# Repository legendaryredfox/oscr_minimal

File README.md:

# oscr_minimal — dumper de cartuchos SNES / NES / Famicom / Mega Drive / GBA

*English summary: [`README.en.md`](README.en.md).*

Shield para **Arduino Mega 2560 (R3)** que lê ROMs e saves de cartuchos pela USB, direto para o PC.
Sem LCD, sem cartão SD. Somente um cartucho por vez.

> **Estado:** 8 placas com projeto KiCad e gerbers, firmware (fork do OSCR com protocolo serial), CLI Python, CLI e GUI em Kotlin (pt-BR, en, ru, zh). **Nenhuma placa foi montada e nada foi testado com cartucho real**: só os testes automáticos no PC e as verificações de hardware abaixo rodaram. Ver "O que foi testado e o que falta".

## Atribuição

Baseado no **Open Source Cartridge Reader (OSCR)** de sanni e comunidade.

- Hardware original: <https://github.com/sanni/cartreader> (licença **CC BY 4.0**).
  Upstream atual: <https://github.com/oscartreader>.
- Firmware original: GPL v3. O firmware deste projeto continuará GPL v3.
- Slots (símbolos e footprints) copiados do OSCR, com alterações descritas em `boards/_lib/README.md`.

Adaptado por: <https://github.com/legendaryredfox/oscr_minimal>

## Conteúdo

| Pasta | O que tem |
|---|---|
| `CLAUDE.md` | Decisões de projeto e fases (também serve de instrução para assistentes de código) |
| `boards/` | **Variantes de hardware**, uma pasta cada (índice e estado em `boards/README.md`). Com projeto KiCad e gerbers: `16_and_8_bits/` (5 slots), `16_bits/` (SNES e Mega Drive) e as de um sistema só ou de dois: `megadrive/`, `snes/`, `nes/`, `famicom/`, `famicom_nes/`, `8_bits/` (NES, Famicom e Master System), `gb_gba/`, `completa/` (sete slots) |
| `boards/<placa>/docs/pinmap.md` | **Fonte da verdade** de cada placa: pino do slot → pino do Mega (o da `16_and_8_bits` é gerado por `tools/gen_pinmap.py`; os das outras são recortes dele) |
| `docs/decisoes.md` | Log de decisões, desvios e pendências |
| `boards/<placa>/hardware-<versão>/` (uma pasta por versão), `fab/`, `docs/` | Projeto KiCad 10 (`dumper.kicad_pro/_sch/_pcb`), gerbers e zip da JLCPCB (`fab/PEDIDO.md` diz como pedir) e `bom.md`/`montagem.md` de cada placa |
| `boards/_lib/` | Símbolos e footprints KiCad compartilhados entre as variantes |
| `docs/referencia/uso.md` | **Guia de uso**: casos de uso, cenários por sistema e solução de problemas |
| `docs/historico/revisao-codigo.md` | Revisão de código da base toda (achados, gravidade, o que foi corrigido) |
| `docs/historico/revisao-ux.md` | Revisão de UX/UI da GUI, da CLI e do hardware, com capturas de tela |
| `docs/referencia/protocolo.md`, `docs/referencia/cli.md`, `docs/referencia/fork-oscr.md`, `docs/referencia/funcoes-oscr.md` | Protocolo serial, guia da CLI, plano do fork do firmware e inventário das funções do OSCR |
| `docs/planos/placa-v1.3-rp2040.md`, `firmware/cic_rp2040/` | CIC do SNES com RP2040-Zero no lugar do PIC (ainda não validado; as placas atuais usam o PIC12F629) |
| `firmware/`, `host/`, `gui/` | Comuns a todas as variantes |
| `database/oscr/` | Base de jogos (24 007, CRC32) do OSCR legado, GPL v3, mais `json/` (bases do `oscr-databases`, 4,9 mil CRC32 novos; o repositório de origem não declara licença, D127); carregada sozinha pelo host e pela GUI (D88, D127) |
| `tools/` | Scripts de hardware: `check_netlist.py` (`--board <placa>`), `export_fab.sh`, `gen_pinmap.py`, `build_lib.py`, `fill_zones.py` e os de cada placa (`megadrive/`, `snes/`, `nes/`, `famicom/`, `famicom_nes/`, `gb_gba/`, `revisao/`); ver `tools/README.md` |

## Adaptadores e repositórios de referência

O código de leitura dos cartuchos vem do OSCR; o que muda por sistema é o adaptador. Fontes consultadas e adaptadores que o firmware reconhece (D136, D137):

| Referência | Para quê |
|---|---|
| <https://github.com/sanni/cartreader> (pasta `hardware/`: `mastersystem_adapter`, `six_slot_adapter`, `*_adapter`) | KiCad dos adaptadores do OSCR; o slot Master System da `megadrive_sms` e os footprints dos slots vêm daí (CC BY 4.0). Arquivado desde 2026-06 |
| <https://github.com/oscartreader/oscr-firmware> | firmware atual do OSCR (GPL v3), base do fork em `firmware/oscr/` |
| <https://github.com/oscartreader/oscr-databases> | bases de jogos e a tabela de chips de flash (`database/oscr/`, D127 e D135; sem licença declarada) |
| <https://github.com/oscartreader/oscr-hardware> | repositório de hardware do novo upstream (vazio em 2026-11-08) |
| <https://github.com/sanni/cartreader/discussions/874> | discussão do adaptador de Game Gear (slot com o conector do RetroSix) |
| <https://www.raphnet.net/electronique/sms_cartridge_programmer/index_en.php> | adaptador **Raphnet** de Master System / SG-1000 (modo `SMSRaphnet` e `SG1000Raphnet` do `SMS.cpp`) |
| <https://forum.retrode.com> | adaptadores **Retrode** (`SMSRetrode`, `GGRetrode` do `SMS.cpp`) |
| <https://www.retrosix.wiki> | pinagem do cartucho de Game Gear e de outros consoles Sega |
| <https://www.smspower.org/maxim/Documents/Pinouts> | pinagem do conector de cartucho do Master System, Mark III e SG-1000 |

**Game Gear e SG-1000** não têm slot próprio nas placas deste projeto: usam adaptador no slot Mega Drive (Retron 3in1, Retrode, Raphnet). Os adaptadores que achei são comerciais; **não encontrei arquivos abertos** (KiCad) deles. Se aparecer um adaptador de código aberto, acrescente o link aqui.

**Tensão dos adaptadores (D138).** Os slots são de 5 V; os flashcarts comuns de Mega Drive e Master System precisam disso (regulam 3,3 V por dentro). As placas v1.1 de Mega Drive, SMS, NES e Famicom têm o **seletor 3,3 V/5 V** (padrão 5 V, `--voltage 3v3` para 3,3 V, alerta ao passar de 3,3 V para 5 V) e o jumper J1 \"TRAVA 3,3 V\"; todas as placas têm o fusível F1 (5×20 mm, 500 mA, em suporte de clipes, troca sem solda) opcional. Adaptador de Game Gear ou cartucho de 3,3 V: confira a tensão do adaptador antes de ligar. Detalhes: `docs/decisoes.md` D138.

## Aviso

- **Use por sua conta e risco.** Hardware e software saem sem garantia (CC BY 4.0 e GPL v3). Placas e firmware são experimentais.
- **Um cartucho por vez.** As placas levam 5 V aos slots de SNES, NES, Famicom e Mega Drive; só o slot GBA é 3,3 V (regulador próprio). Desligue o USB antes de trocar de cartucho e **não use adaptador de GB/GBA** em placa sem o slot GBA.
- **Gravar ROM apaga o chip**, e abortar no meio deixa o chip pela metade. Faça backup do save antes de gravar e comece por cartuchos sem valor (`docs/referencia/uso.md`, seção 7).
- **Uso legal.** A ferramenta serve para fazer cópia de segurança dos cartuchos que você possui. Este repositório não distribui ROMs, BIOS nem chaves; `database/oscr/` só tem listas de nomes e CRC32 do OSCR.
- Nintendo, Super Nintendo, Famicom, Game Boy, Sega, Mega Drive e outros nomes são marcas dos seus donos, citadas só para dizer com o que o projeto é compatível. Sem vínculo com essas empresas nem com o projeto OSCR.

## O que foi testado e o que falta

Cobertura medida (Python 90 %, Kotlin 91,7 % das linhas, C++ puro no PC) e o que nenhum teste alcança: [`docs/referencia/cobertura-testes.md`](docs/referencia/cobertura-testes.md).

**Testado (2026-11-06; tudo no PC, nada em hardware):**

| Parte | O que rodou | Resultado |
|---|---|---|
| Host Python (`host/`) | `cd host && python3 -m pytest -q` | 142 testes passam |
| Firmware, núcleos testáveis no PC | `make -C firmware/oscr/pc-tests test` (protocolo, sessão, plano do SNES, núcleo de flash do Mega Drive etc.) | passam (inclui 21 verificações do plano do SNES e 734 do núcleo de flash do Mega Drive) |
| Firmware, compilação | `pio run -e SerialASCII` em `firmware/oscr` | compila para o Mega 2560 |
| GUI e CLI Kotlin | `cd gui && ./gradlew :shared:jvmTest :desktopApp:compileKotlin :cliApp:compileKotlin` | testes passam, os dois módulos compilam; a janela foi vista só em display virtual |
| Placas (as 8) | ERC, DRC (`--schematic-parity`) e `tools/check_netlist.py --board <placa>` | ERC sem violações; DRC sem erros nem ligações abertas (só avisos de biblioteca e de paridade); netlist confere com o `pinmap.md` de cada placa |
| Gerbers | `16_bits` v1.0 (a antiga `rev2`, D110): zip idêntico ao exportado de `hardware-v1.0`; prévias 3D das placas novas vistas | ok |
| CI (`.github/workflows/ci.yml`) | **nunca executou**; a primeira execução será ao publicar | pendente |

**Falta (nada disso foi feito):**

- **Hardware.**
  - Montar uma placa, medir continuidade e tensão e rodar o primeiro dump (SNES LoROM, NES mapper 0 ou um Mega Drive simples) comparando o CRC32 com o No-Intro.
  - Conferir com as peças reais as medidas dos slots e do módulo Si5351 (D17, D23), o lado da etiqueta (D27, D28) e a altura dos espaçadores (D25).
  - Revisar à mão, no KiCad, os layouts feitos por autoroteador (`megadrive`, `snes`, `nes`, `famicom`, `famicom_nes`, `gb_gba`).
  - A única placa encomendada até agora é a `16_bits` v1.0 original (trilhas de alimentação em 0,3 mm); o repositório guarda no lugar dela a v1.0 revisada, a antiga `rev2` (D110).
- **Firmware.** Os núcleos do OSCR só rodam no AVR, então nenhum teste os cobre. Pontos prováveis de ajuste: tempos de leitura do NES, 1.000.000 baud, `Power::setVoltage` sem VSELECT e o laço de gravação de flash. Roteiro e ordem de risco das gravações em `docs/referencia/uso.md`, seção 7.
- **GUI e CLI.** Serial a 1.000.000 baud em Linux, macOS e Windows, janela estreita, revisão das traduções ru e zh por falantes nativos, empacotamento (deb/AppImage, dmg, msi). `save-write` ainda não relê o save depois de gravar.
- **Funções do OSCR que faltam** (SF Memory, Satellaview, mais mappers do NES, outros sistemas etc.): `docs/referencia/funcoes-oscr.md`.
- **Próximas sessões:** revisão do código, gravar o firmware no Arduino pelo programa desktop e pela CLI (hoje é com o PlatformIO), e testes com as placas.

## CIC do SNES: alternativas ao chip de 8 pinos

As placas com SNES usam hoje o **PIC12F629** (DIP-8, em soquete, gravado com o `snescic-lock-resync.hex` do OSCR). Estamos **estudando alternativas ao CIC de 8 pinos**; a mais avançada é um RP2040-Zero que roda o mesmo programa num interpretador (`docs/planos/placa-v1.3-rp2040.md`, `firmware/cic_rp2040/`, D89). Nada disso foi validado em hardware, e o PIC continua sendo o caminho suportado.

## Verificação

```
python3 tools/check_netlist.py --board <placa>        # netlist do esquemático vs boards/<placa>/docs/pinmap.md
kicad-cli sch erc boards/<placa>/hardware/dumper.kicad_sch                # ERC
kicad-cli pcb drc --schematic-parity boards/<placa>/hardware/dumper.kicad_pcb   # DRC
tools/export_fab.sh <placa> v1.0                      # gerbers, furos, BOM e zip em boards/<placa>/fab/
```

## Recriar o `vendor/` (não versionado)

```
mkdir -p vendor/oscr && cd vendor/oscr
git clone --depth 1 https://github.com/sanni/cartreader legacy
git clone --depth 1 https://github.com/oscartreader/oscr-firmware firmware
```

`tools/gen_pinmap.py` lê `vendor/oscr/legacy/` (pinout.ods, esquemáticos KiCad, firmware).

## Contribuir

Veja `CONTRIBUTING.md`. Testes em hardware são o que mais ajuda: abra uma issue com o modelo "Teste em hardware" (placa, cartucho, versão, logs).

## Requisitos

KiCad 10.0.8 (`kicad-cli`), Python 3.11+. Para refazer layouts: o servidor MCP do KiCad (Python com `pcbnew`) e o Freerouting; ver `tools/README.md` e `docs/decisoes.md` (D92 a D101).

## Licença

Hardware: **CC BY 4.0**. Software: **GPL v3 ou posterior**. Mesmas licenças do OSCR; ver `LICENSE.md`.

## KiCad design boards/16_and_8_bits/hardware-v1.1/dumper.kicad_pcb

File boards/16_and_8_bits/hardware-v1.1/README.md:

# 16_and_8_bits v1.1

Versão **v1.1** da placa [`16_and_8_bits`](../README.md): shield 100% THT para Arduino Mega 2560 R3, só USB. Esta é a versão mais nova.

| | |
|---|---|
| Slots | SNES (62p), NES (72p), Famicom (60p), Mega Drive (64p), todos a 5 V, e GBA (32p, SMD, 1,5 mm) a 3,3 V (regulador U3) |
| Circuitos | Si5351 em header fêmea e PIC12F629 (CIC do SNES) em soquete. |
| Tamanho | 144,1 × 134,1 mm |
| Projeto KiCad | [`hardware-v1.1/`](.) (`dumper.kicad_pro`, `.kicad_sch`, `.kicad_pcb`) |
| Fábrica (JLCPCB) | `../fab/gerbers-v1.1/`, `../fab/dumper-v1.1-jlcpcb.zip` |
| Renders | `render-cima.png`, `render-baixo.png` |
| Estado | Nada montado nem testado com cartucho; revisar o layout no KiCad antes de encomendar |

## Troca de cartucho

O 5V dos slots vai direto do Mega e **não é cortado por software** (o desligamento por software foi retirado, D139). Para trocar o cartucho, **desligue a placa tirando o cabo USB** do Mega; nunca com a USB ligada.

## Proteção de corrente e tensão (D138)

**F1: fusível de vidro 5×20 mm de 500 mA (ação rápida) em suporte de clipes, opcional.** O suporte é de furo passante (Littelfuse série 100 ou equivalente) e o fusível queimado se troca **sem solda**; fica em série com o 5 V que a placa recebe do Mega Um curto no cartucho queima o fusível e protege a placa, o Mega e a porta USB. A queda é de 0,1 a 0,2 V a 200 mA (o SA-1 do SNES continua abaixo de ~5,2 V). **Sem o fusível no suporte a placa fica sem 5 V** (um fio no lugar dele também serve). Ele limita corrente e não protege contra tensão errada.

**Seletor de tensão 3,3 V/5 V dos slots NES, Famicom, Mega Drive** (LDO LD1117V33 em TO-220, Q4 de bypass, Q5 de carga, comando no D18; sem resistores em série entre o Mega e os slots, D140). **Padrão: 5 V**; 3,3 V só quando o usuário pede (`--voltage 3v3`, ou o botão da GUI). Passar de 3,3 V para 5 V mostra um alerta e pede confirmação. Os outros slots e o Si5351/PIC ficam direto no 5 V. Cartuchos de 3,3 V ligados em 5 V podem queimar, e em 3,3 V as saídas do Mega continuam em 5 V: **confira a tensão que o cartucho suporta antes de inserir**.

**J1: jumper "TRAVA 3,3 V", opcional.** Fechado, prende o gate do Q4 no 5 V e o slot nunca passa de 3,3 V, mesmo com erro de software ou de GUI: é a única defesa independente do firmware. Aberto, o seletor funciona normalmente.

## Particularidades desta versão

A v1.0 mais a proteção: seletor de tensão 3,3 V/5 V nos slots NES, Famicom e Mega Drive (o SNES fica em 5 V por causa do SA-1; o GBA tem o U3), J1 (trava de 3,3 V). Seletor transplantado da `8_bits` v1.1; roteada de novo pelo Freerouting (**revisar o layout no KiCad**). Nada montado nem testado.

## O que muda em relação à v1.0

| Peça | Referências | Antes | Agora |
|---|---|---|---|
| 10u/16V | C11 | 0 | 1 |
| TRAVA 3,3 V | J1 | 0 | 1 |
| IRF9540N | Q1 | 0 | 1 |
| 2N7000 | Q2 | 0 | 1 |
| 100k | R3 | 0 | 1 |
| 1k | R4 | 0 | 1 |
| 220R | R5 | 0 | 1 |
| LD1117V33 | U4 | 0 | 1 |
| 100n | C2,C3,C4,C5,C6,C9,C10 | 6 | 7 |

## Lista de peças

| Referências | Valor | Footprint | Qtd |
|---|---|---|---|
| A1 | Mega2560_R3_Shield | `dumper:Mega2560_R3_Shield` | 1 |
| C1 | 470u/16V | `Capacitor_THT:CP_Radial_D8.0mm_P3.50mm` | 1 |
| C2,C3,C4,C5,C6,C9,C10 | 100n | `Capacitor_THT:C_Disc_D5.0mm_W2.5mm_P5.00mm` | 7 |
| C7,C8 | 1u | `Capacitor_THT:C_Disc_D5.0mm_W2.5mm_P5.00mm` | 2 |
| C11 | 10u/16V | `Capacitor_THT:CP_Radial_D5.0mm_P2.00mm` | 1 |
| D1 | LED 3mm | `LED_THT:LED_D3.0mm` | 1 |
| F1 | Fusivel 5x20 500mA | `Fuse:Fuseholder_Littelfuse_100_series_5x20mm` | 1 |
| FC1 | FC_Slot | `dumper:FC_Slot` | 1 |
| FLG1,FLG2 | PWR_FLAG | `` | 2 |
| GBA1 | GBA_Slot | `dumper:GBA_Slot` | 1 |
| J1 | TRAVA 3,3 V | `Connector_PinHeader_2.54mm:PinHeader_1x02_P2.54mm_Vertical` | 1 |
| MD1 | MD_Slot | `dumper:MD_Slot` | 1 |
| NES1 | NES_Slot | `dumper:NES_Slot` | 1 |
| Q1 | IRF9540N | `Package_TO_SOT_THT:TO-220-3_Vertical` | 1 |
| Q2 | 2N7000 | `Package_TO_SOT_THT:TO-92_Inline` | 1 |
| R1 | 220R | `Resistor_THT:R_Axial_DIN0207_L6.3mm_D2.5mm_P10.16mm_Horizontal` | 1 |
| R2 | 1k | `Resistor_THT:R_Axial_DIN0207_L6.3mm_D2.5mm_P10.16mm_Horizontal` | 1 |
| R3 | 100k | `Resistor_THT:R_Axial_DIN0204_L3.6mm_D1.6mm_P2.54mm_Vertical` | 1 |
| R4 | 1k | `Resistor_THT:R_Axial_DIN0204_L3.6mm_D1.6mm_P2.54mm_Vertical` | 1 |
| R5 | 220R | `Resistor_THT:R_Axial_DIN0204_L3.6mm_D1.6mm_P2.54mm_Vertical` | 1 |
| SNES1 | SNES_Slot | `dumper:SNES_Slot` | 1 |
| U1 | Si5351_Module | `Connector_PinSocket_2.54mm:PinSocket_1x07_P2.54mm_Vertical` | 1 |
| U2 | PIC12F629 (snescic-lock-resync) | `Package_DIP:DIP-8_W7.62mm_Socket` | 1 |
| U3 | MCP1700-3302E/TO (3,3 V) | `Package_TO_SOT_THT:TO-92` | 1 |
| U4 | LD1117V33 | `Package_TO_SOT_THT:TO-220-3_Vertical` | 1 |

Gerada do esquemático desta versão (`kicad-cli sch export bom`). Peças marcadas DNP ou opcionais: `docs/componentes-opcionais.md` da placa.

## Verificação e fábrica (da raiz do repositório)

```
python3 tools/check_netlist.py --board 16_and_8_bits boards/16_and_8_bits/hardware-v1.1/dumper.kicad_sch
kicad-cli sch erc boards/16_and_8_bits/hardware-v1.1/dumper.kicad_sch
kicad-cli pcb drc boards/16_and_8_bits/hardware-v1.1/dumper.kicad_pcb
tools/export_fab.sh 16_and_8_bits v1.1
tools/render_board.sh 16_and_8_bits v1.0 v1.1
```

Mais: [README da placa](../README.md), [`docs/`](../docs/).

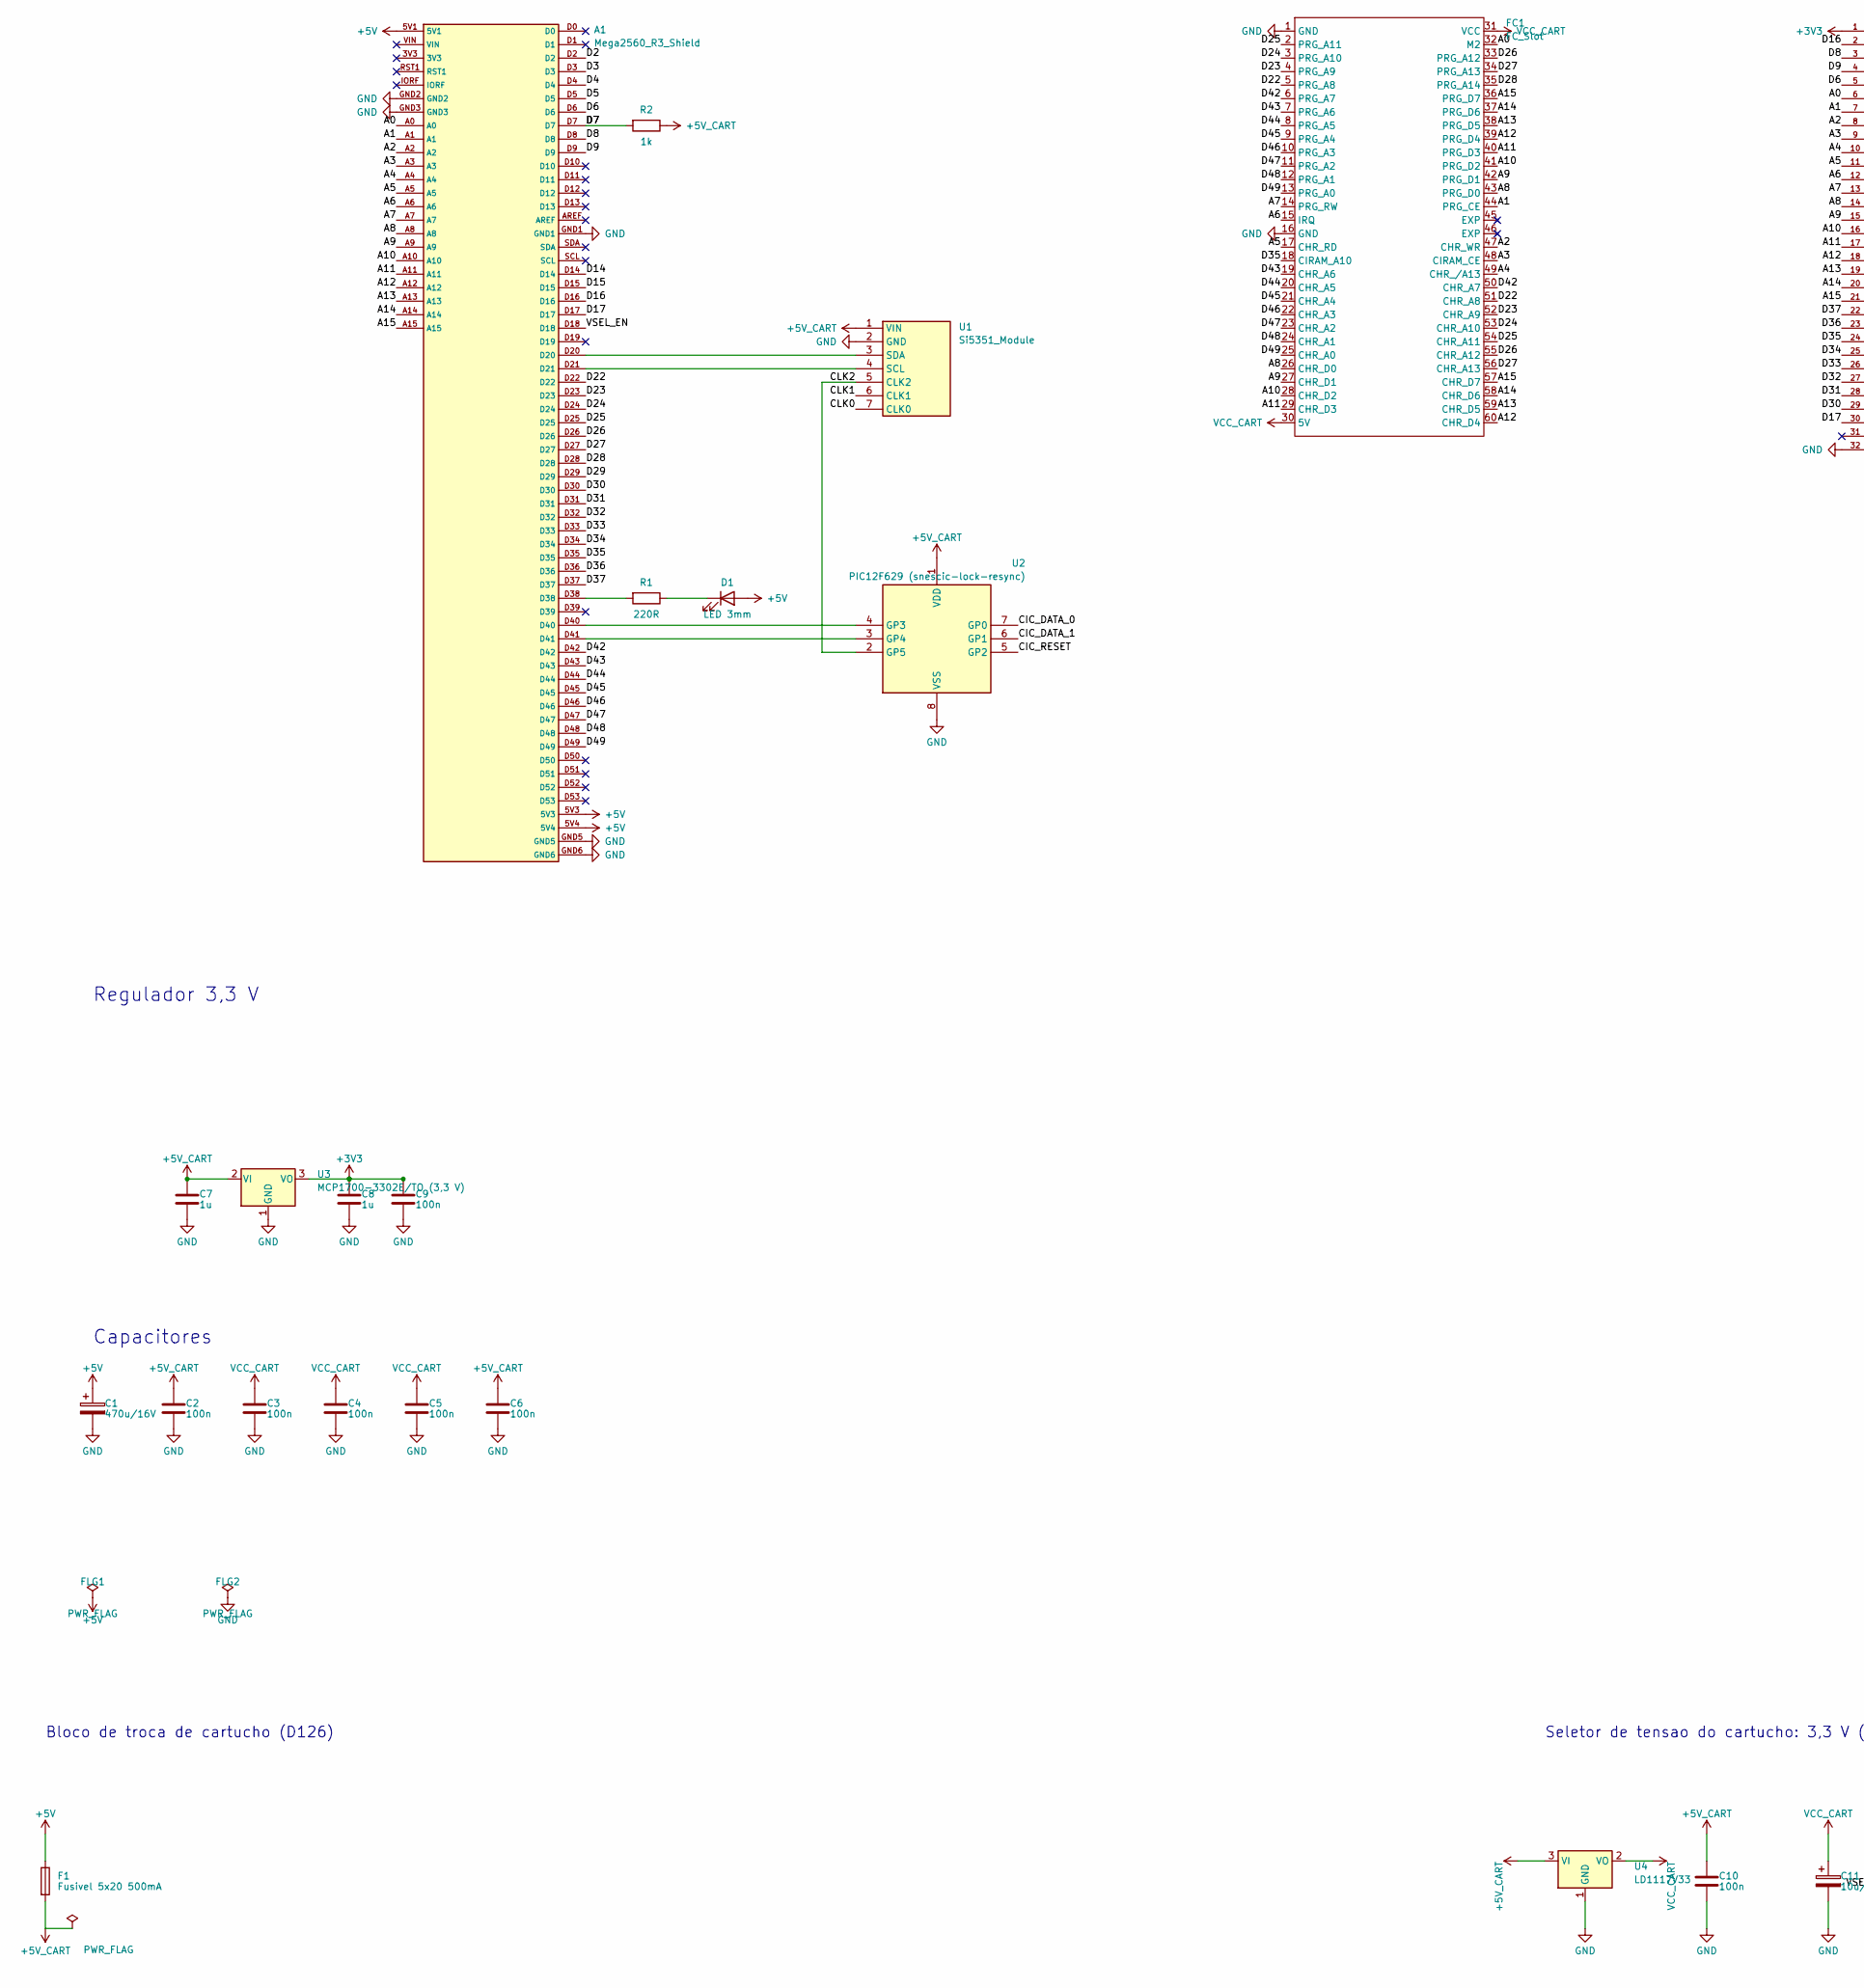
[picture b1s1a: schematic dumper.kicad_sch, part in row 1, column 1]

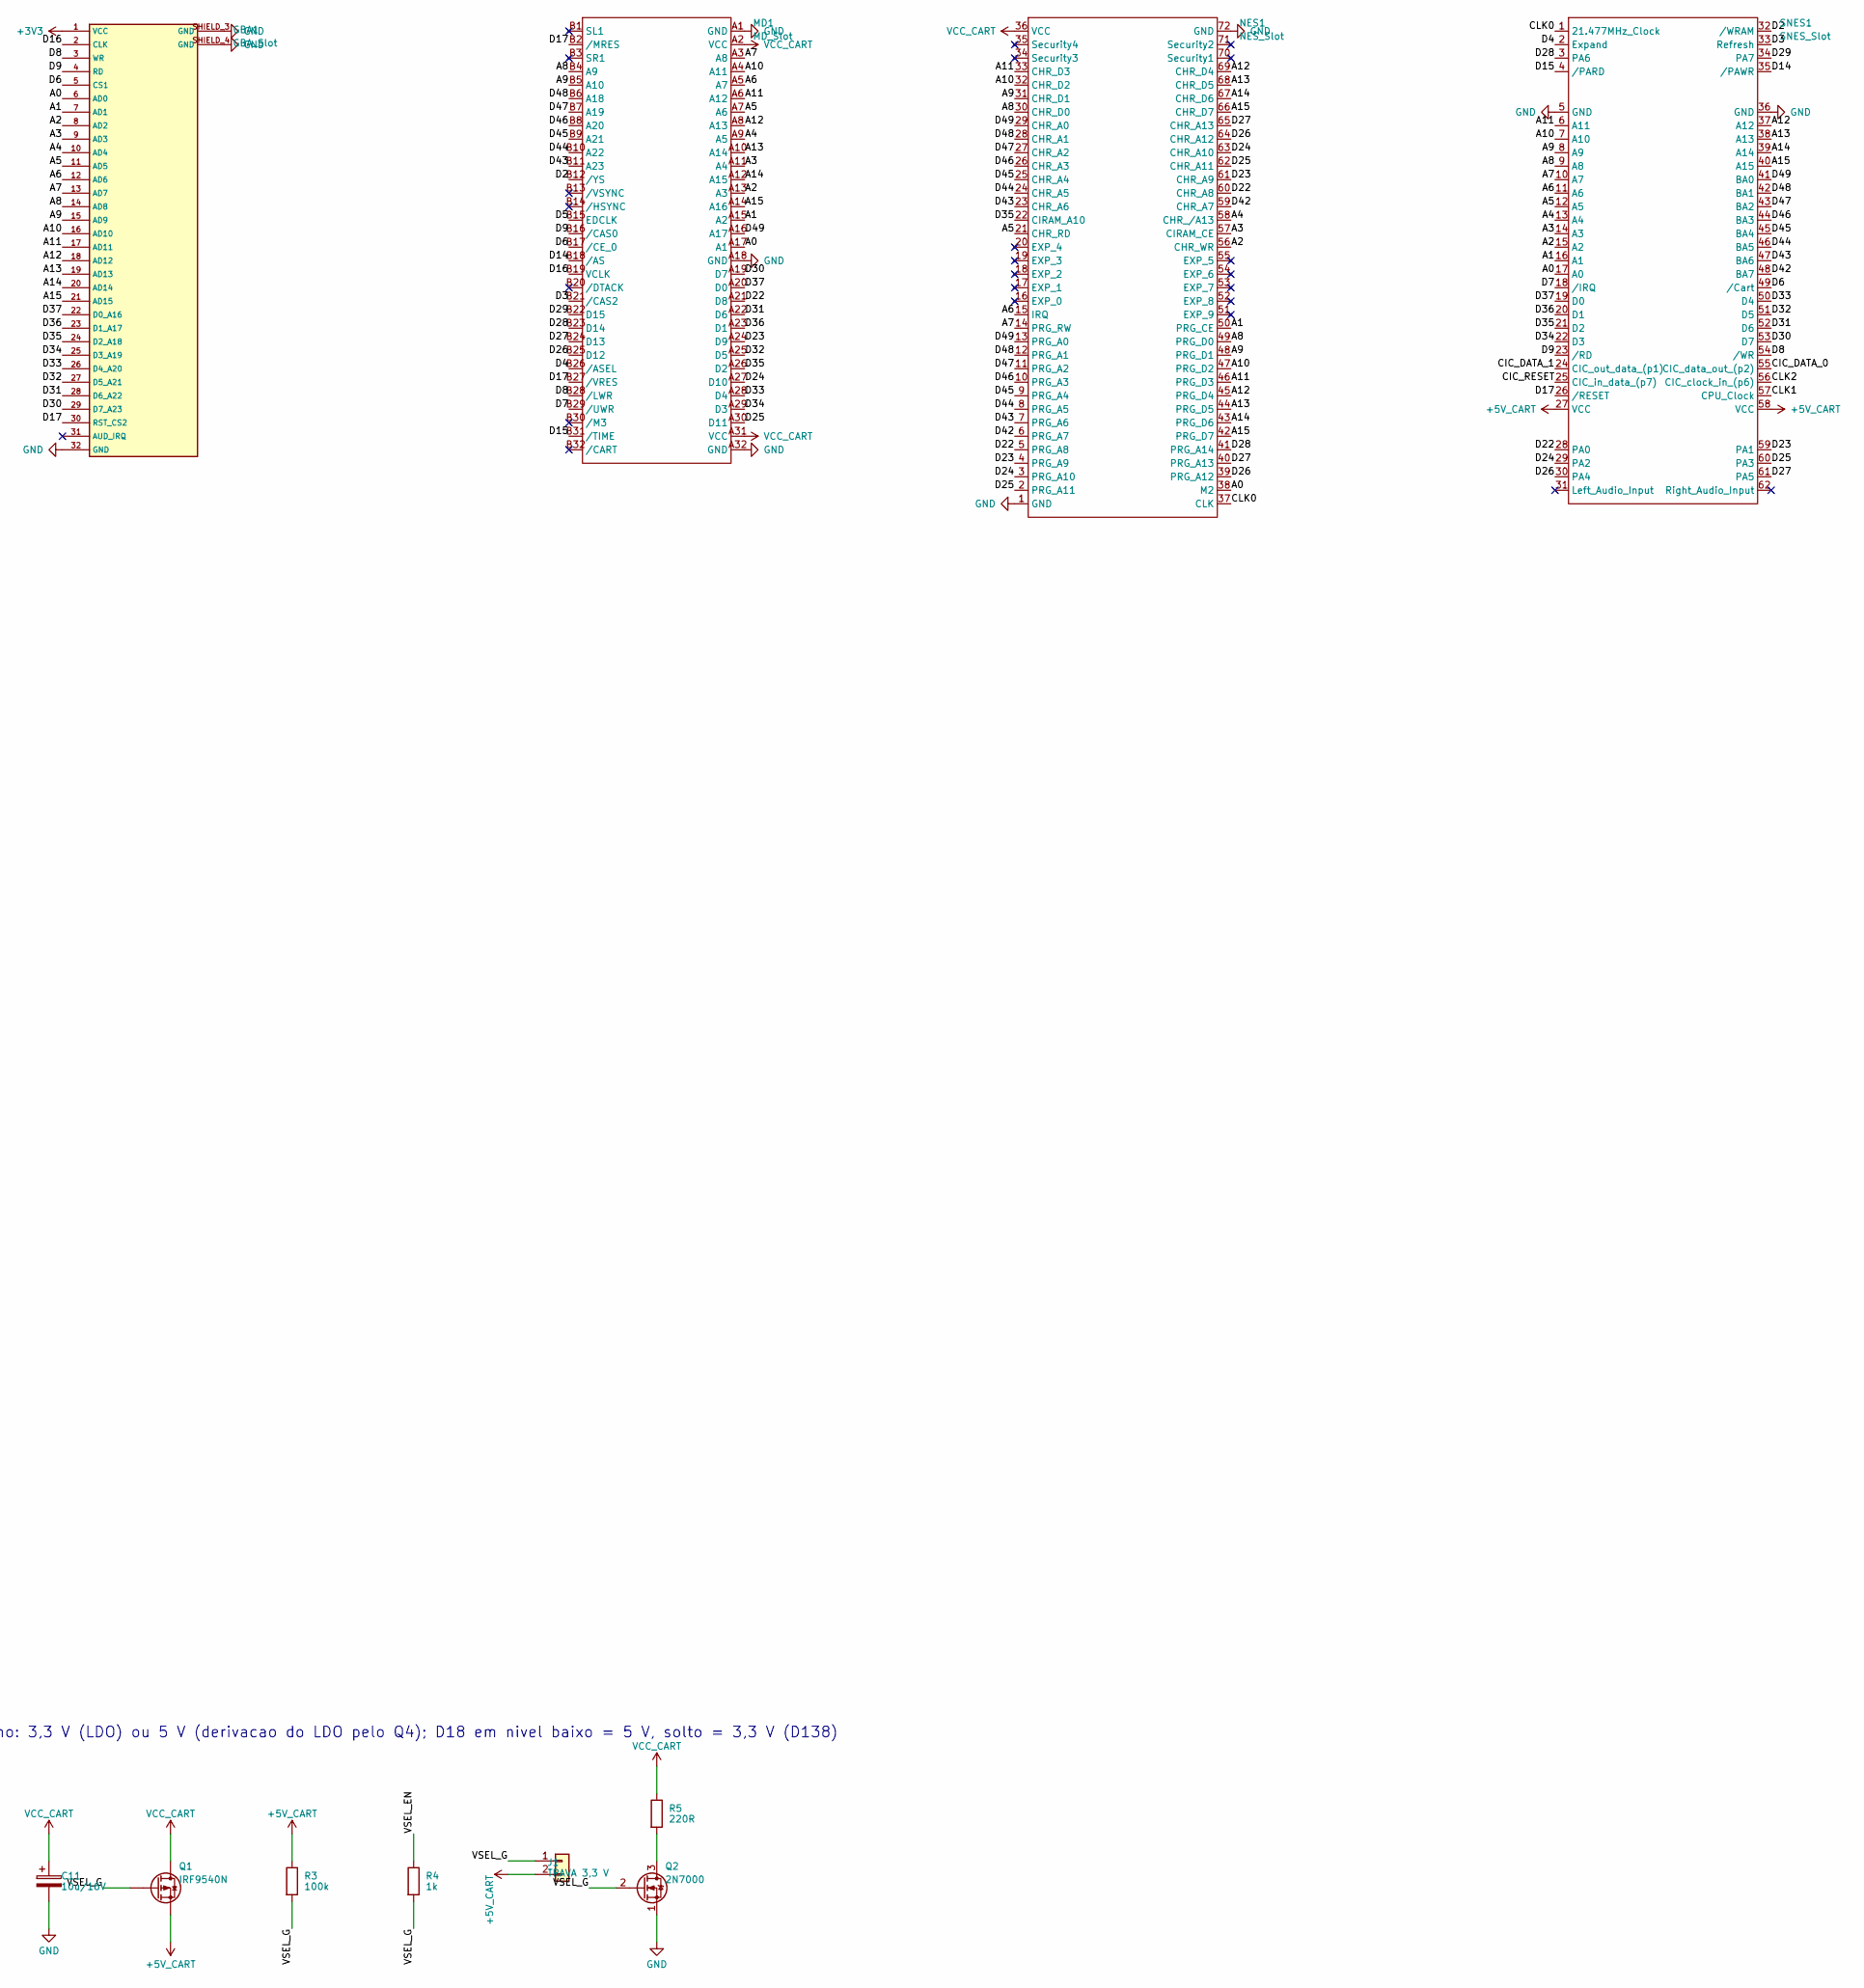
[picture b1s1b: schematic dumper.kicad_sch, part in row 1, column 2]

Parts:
A1: Mega2560_R3_Shield
C1: 470u/16V; CP_Radial_D8.0mm_P3.50mm
C2, C3, C4, C5, C6, C9, C10: 100n; C_Disc_D5.0mm_W2.5mm_P5.00mm
C7, C8: 1u; C_Disc_D5.0mm_W2.5mm_P5.00mm
C11: 10u/16V; CP_Radial_D5.0mm_P2.00mm
D1: LED 3mm; LED_D3.0mm
F1: Fusivel 5x20 500mA; Fuseholder_Littelfuse_100_series_5x20mm
FC1: FC_Slot
FLG1, FLG2, FLG3: PWR_FLAG
GBA1: GBA_Slot
J1: TRAVA 3,3 V; PinHeader_1x02_P2.54mm_Vertical
MD1: MD_Slot
NES1: NES_Slot
Q1: IRF9540N; TO-220-3_Vertical
Q2: 2N7000; TO-92_Inline
R1: 220R; R_Axial_DIN0207_L6.3mm_D2.5mm_P10.16mm_Horizontal
R2: 1k; R_Axial_DIN0207_L6.3mm_D2.5mm_P10.16mm_Horizontal
R3: 100k; R_Axial_DIN0204_L3.6mm_D1.6mm_P2.54mm_Vertical
R4: 1k; R_Axial_DIN0204_L3.6mm_D1.6mm_P2.54mm_Vertical
R5: 220R; R_Axial_DIN0204_L3.6mm_D1.6mm_P2.54mm_Vertical
SNES1: SNES_Slot
U1: Si5351_Module; PinSocket_1x07_P2.54mm_Vertical
U2: PIC12F629 (snescic-lock-resync); DIP-8_W7.62mm_Socket
U3: MCP1700-3302E/TO (3,3 V); TO-92
U4: LD1117V33; TO-220-3_Vertical

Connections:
+3V3: C8.1, C9.1, GBA1.1 (VCC), U3.3 (VO)
+5V: A1.5V1, A1.5V3, A1.5V4, C1.1, D1.2 (A), F1.1, FLG1.1
+5V_CART: C2.1, C6.1, C7.1, C10.1, F1.2, FLG3.1, J1.2, Q1.3 (S), R2.1, R3.1, SNES1.27 (VCC), SNES1.58 (VCC), U1.1 (VIN), U2.1 (VDD), U3.2 (VI), U4.3 (VI)
/A0: A1.A0, FC1.32 (M2), GBA1.6 (AD0), MD1.A17 (A1), NES1.38 (M2), SNES1.17 (A0)
/A1: A1.A1, FC1.44 (PRG_CE), GBA1.7 (AD1), MD1.A15 (A2), NES1.50 (PRG_CE), SNES1.16 (A1)
/A2: A1.A2, FC1.47 (CHR_WR), GBA1.8 (AD2), MD1.A13 (A3), NES1.56 (CHR_WR), SNES1.15 (A2)
/A3: A1.A3, FC1.48 (CIRAM_CE), GBA1.9 (AD3), MD1.A11 (A4), NES1.57 (CIRAM_CE), SNES1.14 (A3)
/A4: A1.A4, FC1.49 (CHR_/A13), GBA1.10 (AD4), MD1.A9 (A5), NES1.58 (CHR_/A13), SNES1.13 (A4)
/A5: A1.A5, FC1.17 (CHR_RD), GBA1.11 (AD5), MD1.A7 (A6), NES1.21 (CHR_RD), SNES1.12 (A5)
/A6: A1.A6, FC1.15 (IRQ), GBA1.12 (AD6), MD1.A5 (A7), NES1.15 (IRQ), SNES1.11 (A6)
/A7: A1.A7, FC1.14 (PRG_RW), GBA1.13 (AD7), MD1.A3 (A8), NES1.14 (PRG_RW), SNES1.10 (A7)
/A8: A1.A8, FC1.26 (CHR_D0), FC1.43 (PRG_D0), GBA1.14 (AD8), MD1.B4 (A9), NES1.30 (CHR_D0), NES1.49 (PRG_D0), SNES1.9 (A8)
/A9: A1.A9, FC1.27 (CHR_D1), FC1.42 (PRG_D1), GBA1.15 (AD9), MD1.B5 (A10), NES1.31 (CHR_D1), NES1.48 (PRG_D1), SNES1.8 (A9)
/A10: A1.A10, FC1.28 (CHR_D2), FC1.41 (PRG_D2), GBA1.16 (AD10), MD1.A4 (A11), NES1.32 (CHR_D2), NES1.47 (PRG_D2), SNES1.7 (A10)
/A11: A1.A11, FC1.29 (CHR_D3), FC1.40 (PRG_D3), GBA1.17 (AD11), MD1.A6 (A12), NES1.33 (CHR_D3), NES1.46 (PRG_D3), SNES1.6 (A11)
/A12: A1.A12, FC1.39 (PRG_D4), FC1.60 (CHR_D4), GBA1.18 (AD12), MD1.A8 (A13), NES1.45 (PRG_D4), NES1.69 (CHR_D4), SNES1.37 (A12)
/A13: A1.A13, FC1.38 (PRG_D5), FC1.59 (CHR_D5), GBA1.19 (AD13), MD1.A10 (A14), NES1.44 (PRG_D5), NES1.68 (CHR_D5), SNES1.38 (A13)
/A14: A1.A14, FC1.37 (PRG_D6), FC1.58 (CHR_D6), GBA1.20 (AD14), MD1.A12 (A15), NES1.43 (PRG_D6), NES1.67 (CHR_D6), SNES1.39 (A14)
/A15: A1.A15, FC1.36 (PRG_D7), FC1.57 (CHR_D7), GBA1.21 (AD15), MD1.A14 (A16), NES1.42 (PRG_D7), NES1.66 (CHR_D7), SNES1.40 (A15)
/CIC_DATA_0: SNES1.55 (CIC_data_out_(p2)), U2.7 (GP0)
/CIC_DATA_1: SNES1.24 (CIC_out_data_(p1)), U2.6 (GP1)
/CIC_RESET: SNES1.25 (CIC_in_data_(p7)), U2.5 (GP2)
/CLK0: NES1.37 (CLK), SNES1.1 (21.477MHz_Clock), U1.7 (CLK0)
/CLK1: SNES1.57 (CPU_Clock), U1.6 (CLK1)
/CLK2: SNES1.56 (CIC_clock_in_(p6)), U1.5 (CLK2), U2.2 (GP5)
/D2: A1.D2, MD1.B12 (/YS), SNES1.32 (/WRAM)
/D3: A1.D3, MD1.B21 (/CAS2), SNES1.33 (Refresh)
/D4: A1.D4, MD1.B26 (/ASEL), SNES1.2 (Expand)
/D5: A1.D5, MD1.B15 (EDCLK)
/D6: A1.D6, GBA1.5 (CS1), MD1.B17 (/CE_0), SNES1.49 (/Cart)
/D7: A1.D7, MD1.B29 (/UWR), R2.2, SNES1.18 (/IRQ)
/D8: A1.D8, GBA1.3 (WR), MD1.B28 (/LWR), SNES1.54 (/WR)
/D9: A1.D9, GBA1.4 (RD), MD1.B16 (/CAS0), SNES1.23 (/RD)
/D14: A1.D14, MD1.B18 (/AS), SNES1.35 (/PAWR)
/D15: A1.D15, MD1.B31 (/TIME), SNES1.4 (/PARD)
/D16: A1.D16, GBA1.2 (CLK), MD1.B19 (VCLK)
/D17: A1.D17, GBA1.30 (RST_CS2), MD1.B2 (/MRES), MD1.B27 (/VRES), SNES1.26 (/RESET)
/D22: A1.D22, FC1.5 (PRG_A8), FC1.51 (CHR_A8), MD1.A21 (D8), NES1.5 (PRG_A8), NES1.60 (CHR_A8), SNES1.28 (PA0)
/D23: A1.D23, FC1.4 (PRG_A9), FC1.52 (CHR_A9), MD1.A24 (D9), NES1.4 (PRG_A9), NES1.61 (CHR_A9), SNES1.59 (PA1)
/D24: A1.D24, FC1.3 (PRG_A10), FC1.53 (CHR_A10), MD1.A27 (D10), NES1.3 (PRG_A10), NES1.63 (CHR_A10), SNES1.29 (PA2)
/D25: A1.D25, FC1.2 (PRG_A11), FC1.54 (CHR_A11), MD1.A30 (D11), NES1.2 (PRG_A11), NES1.62 (CHR_A11), SNES1.60 (PA3)
/D26: A1.D26, FC1.33 (PRG_A12), FC1.55 (CHR_A12), MD1.B25 (D12), NES1.39 (PRG_A12), NES1.64 (CHR_A12), SNES1.30 (PA4)
/D27: A1.D27, FC1.34 (PRG_A13), FC1.56 (CHR_A13), MD1.B24 (D13), NES1.40 (PRG_A13), NES1.65 (CHR_A13), SNES1.61 (PA5)
/D28: A1.D28, FC1.35 (PRG_A14), MD1.B23 (D14), NES1.41 (PRG_A14), SNES1.3 (PA6)
/D29: A1.D29, MD1.B22 (D15), SNES1.34 (PA7)
/D30: A1.D30, GBA1.29 (D7_A23), MD1.A19 (D7), SNES1.53 (D7)
/D31: A1.D31, GBA1.28 (D6_A22), MD1.A22 (D6), SNES1.52 (D6)
/D32: A1.D32, GBA1.27 (D5_A21), MD1.A25 (D5), SNES1.51 (D5)
/D33: A1.D33, GBA1.26 (D4_A20), MD1.A28 (D4), SNES1.50 (D4)
/D34: A1.D34, GBA1.25 (D3_A19), MD1.A29 (D3), SNES1.22 (D3)
/D35: A1.D35, FC1.18 (CIRAM_A10), GBA1.24 (D2_A18), MD1.A26 (D2), NES1.22 (CIRAM_A10), SNES1.21 (D2)
/D36: A1.D36, GBA1.23 (D1_A17), MD1.A23 (D1), SNES1.20 (D1)
/D37: A1.D37, GBA1.22 (D0_A16), MD1.A20 (D0), SNES1.19 (D0)
/D42: A1.D42, FC1.6 (PRG_A7), FC1.50 (CHR_A7), NES1.6 (PRG_A7), NES1.59 (CHR_A7), SNES1.48 (BA7)
/D43: A1.D43, FC1.7 (PRG_A6), FC1.19 (CHR_A6), MD1.B11 (A23), NES1.7 (PRG_A6), NES1.23 (CHR_A6), SNES1.47 (BA6)
/D44: A1.D44, FC1.8 (PRG_A5), FC1.20 (CHR_A5), MD1.B10 (A22), NES1.8 (PRG_A5), NES1.24 (CHR_A5), SNES1.46 (BA5)
/D45: A1.D45, FC1.9 (PRG_A4), FC1.21 (CHR_A4), MD1.B9 (A21), NES1.9 (PRG_A4), NES1.25 (CHR_A4), SNES1.45 (BA4)
/D46: A1.D46, FC1.10 (PRG_A3), FC1.22 (CHR_A3), MD1.B8 (A20), NES1.10 (PRG_A3), NES1.26 (CHR_A3), SNES1.44 (BA3)
/D47: A1.D47, FC1.11 (PRG_A2), FC1.23 (CHR_A2), MD1.B7 (A19), NES1.11 (PRG_A2), NES1.27 (CHR_A2), SNES1.43 (BA2)
/D48: A1.D48, FC1.12 (PRG_A1), FC1.24 (CHR_A1), MD1.B6 (A18), NES1.12 (PRG_A1), NES1.28 (CHR_A1), SNES1.42 (BA1)
/D49: A1.D49, FC1.13 (PRG_A0), FC1.25 (CHR_A0), MD1.A16 (A17), NES1.13 (PRG_A0), NES1.29 (CHR_A0), SNES1.41 (BA0)
/VSEL_EN: A1.D18, R4.1
/VSEL_G: J1.1, Q1.1 (G), Q2.2 (G), R3.2, R4.2
GND: A1.GND1, A1.GND2, A1.GND3, A1.GND5, A1.GND6, C1.2, C2.2, C3.2, C4.2, C5.2, C6.2, C7.2, C8.2, C9.2, C10.2, C11.2, FC1.1 (GND), FC1.16 (GND), FLG2.1, GBA1.32 (GND), GBA1.SHIELD_3 (GND), GBA1.SHIELD_4 (GND), MD1.A1 (GND), MD1.A18 (GND), MD1.A32 (GND), NES1.1 (GND), NES1.72 (GND), Q2.1 (S), SNES1.5 (GND), SNES1.36 (GND), U1.2 (GND), U2.8 (VSS), U3.1 (GND), U4.1 (GND)
unnamed: A1.D38, R1.2
unnamed: D1.1 (K), R1.1
unnamed: Q2.3 (D), R5.2
unnamed: A1.D21, U1.4 (SCL)
unnamed: A1.D20, U1.3 (SDA)
unnamed: A1.D40, U2.4 (GP3)
unnamed: A1.D41, U2.3 (GP4)
VCC_CART: C3.1, C4.1, C5.1, C11.1, FC1.30 (5V), FC1.31 (VCC), MD1.A2 (VCC), MD1.A31 (VCC), NES1.36 (VCC), Q1.2 (D), R5.1, U4.2 (VO)

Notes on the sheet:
Regulador 3,3 V
Capacitores
Bloco de troca de cartucho (D126)
Seletor de tensao do cartucho: 3,3 V (LDO) ou 5 V (derivacao do LDO pelo Q4); D18 em nivel baixo = 5 V, solto = 3,3 V (D138)

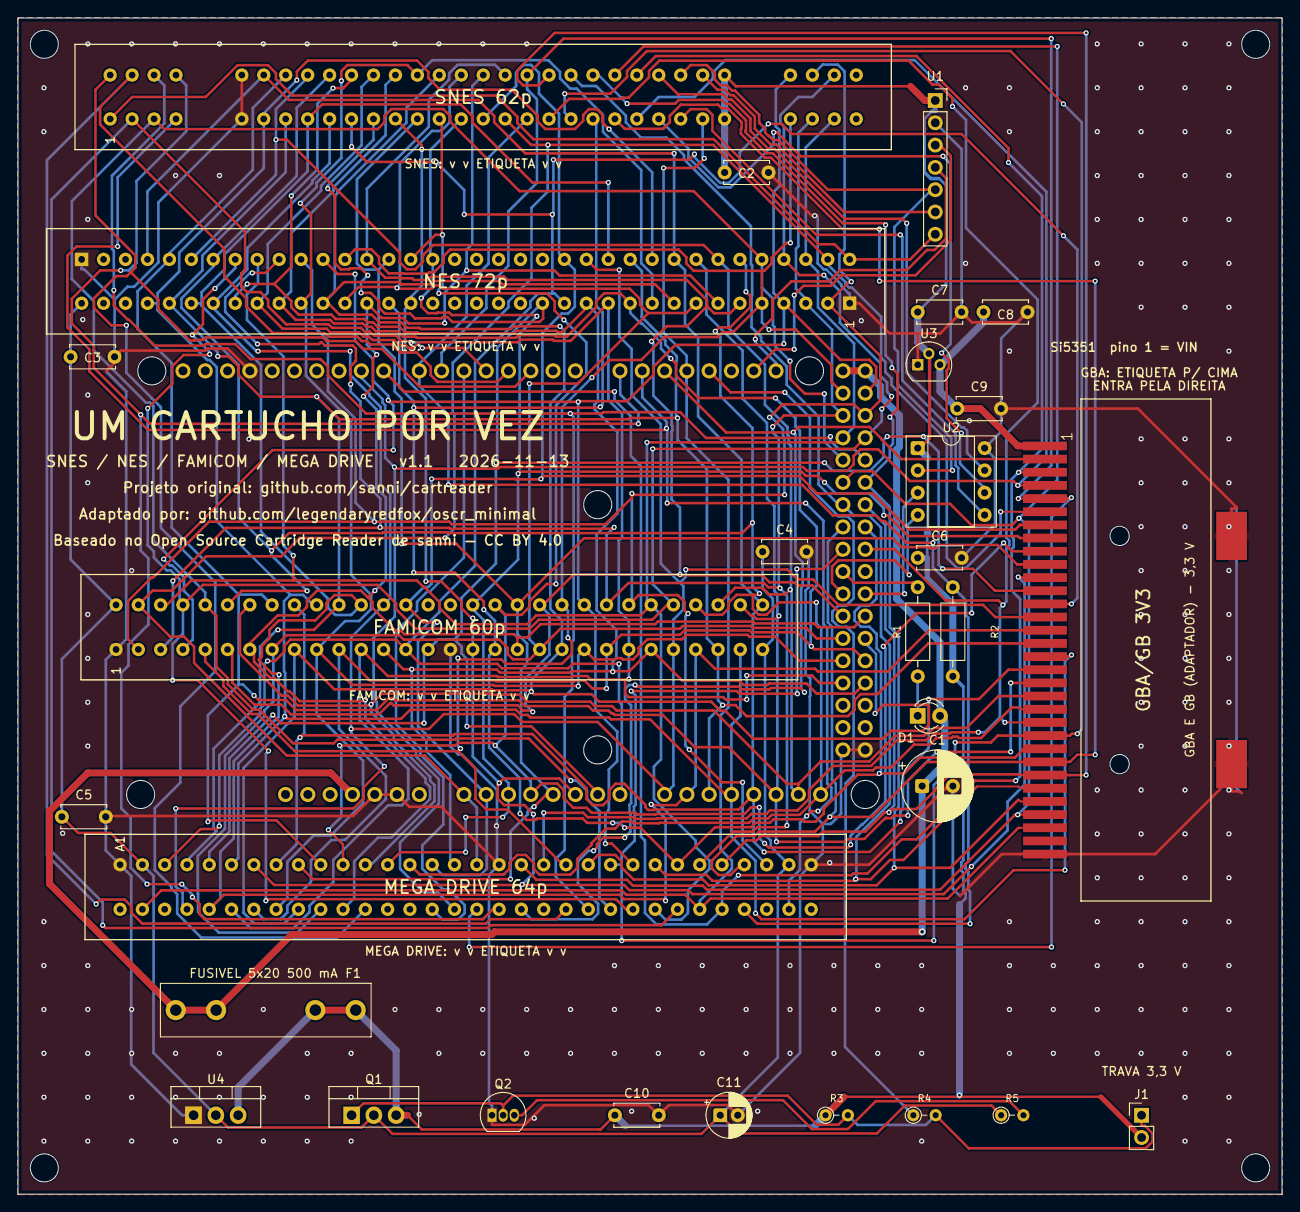
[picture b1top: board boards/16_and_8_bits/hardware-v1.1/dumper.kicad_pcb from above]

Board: 2 copper layers, 144.0 x 134.0 mm, 35 parts (0 on the bottom side), 72 nets.

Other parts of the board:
MH1, MH2, MH3, MH4: MountingHole_3.2mm; MountingHole_3.2mm_M3

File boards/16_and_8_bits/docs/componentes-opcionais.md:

# 16_and_8_bits — componentes que podem ser retirados e o que se perde

Placa de 5 slots v1.0: SNES, NES, Famicom, Mega Drive e GBA (`boards/16_and_8_bits/`). Sem chave de 5 V (Q1) nem proteção das linhas. Um cartucho por vez.

> **Nada aqui foi testado em hardware.** Fontes: `docs/bom.md`, `pinmap.md`, firmware, D54 e `docs/referencia/limites-gb.md`.

| Peça | Retirar? | O que deixa de funcionar | Jogos afetados |
|---|---|---|---|
| **U2** PIC12F629 (CIC) + soquete | **Perde o SA-1** | O PIC emula o CIC do SNES; o SA-1 só responde com ele rodando | Só **SA-1** (Super Mario RPG, Kirby Super Star, Kirby's Dream Land 3, Jikkyou Oshaberi Parodius, Dragon Ball Z: Hyper Dimension e outros; lista não exaustiva em `snes/docs/componentes-opcionais.md`). NES, Famicom, Mega Drive e GBA não usam |
| **U1** módulo Si5351 | **Perde o SA-1**; o PIC fica sem clock | SNES: clock mestre (pino 1), CPU (57) e CIC (56). NES: o `CLK0` vai ao pino 37, mas o firmware atual não o usa | SA-1; futuros Satellaview e SF Memory. NES: nenhum conhecido |
| **R2** 1 kΩ (pull-up de D7, `/IRQ` do SNES) | Sim, com cuidado | `/IRQ` solta. D7 também é o `/UWR` do Mega Drive (pino B29); o pull-up estava no HW5 | Nenhum conhecido. Inferência |
| **U3** MCP1700-3302E + **C7**, **C8** (1 µF) + **C9** | **Perde o GBA, o GB e o GBC** | O slot GBA só tem 3,3 V, vindo do U3. Sem ele, sem energia no slot. Nunca ligar o GBA ao 5 V | Todos os GBA, GB e GBC. SNES, NES, Famicom e Mega Drive não dependem (5 V direto) |
| **D1** LED + **R1** 220 Ω | Sim | Indicação de atividade | Nenhum |
| **C2** SNES, **C3** NES, **C4** Famicom, **C5** Mega Drive, **C9** GBA, **C6** PIC (100 nF) | Não recomendado | Desacoplamento do slot ou do PIC. Sem eles, leitura errada possível (CRC variável) | Mais provável: SA-1, ROM grande (SSF2), GBA com Flash. Inferência |
| **C1** 470 µF | Não recomendado | Reserva do 5 V | Todos |

## Montagens parciais

Como os slots dividem os mesmos barramentos, pode-se montar só os slots que o usuário vai usar; os demais ficam vazios sem prejuízo, **menos** o desacoplamento de cada slot (montar o capacitor do slot usado). Sem PIC e sem Si5351 a placa lê tudo menos SA-1. Sem U3 e seus capacitores perde-se tudo do GBA (inclusive GB/GBC por adaptador), mas o slot GBA pode continuar vazio.

Sobre GB/GBC a 3,3 V: ver `docs/referencia/limites-gb.md` (alguns GB antigos podem falhar; jumper para 5 V só para GB/GBC, nunca GBA).

## F1, J1 e seletor de tensão (D138)

<!-- d138 -->

| Peça | Opcional? | O que se perde sem ela |
|---|---|---|
| F1 (suporte e fusível 5×20 mm, 500 mA) | **Sim**, mas sem o fusível no suporte a placa não tem 5 V (um fio no lugar dele também serve) | só a proteção contra curto no cartucho (placa, Mega e USB) |

**F1**: fusível de vidro **5×20 mm, 500 mA, ação rápida**, em suporte de clipes de furo passante (Littelfuse série 100 ou equivalente): o fusível queimado se troca **sem solda**. Fica em série com o 5 V que a placa recebe do Mega. Queda de 0,1 a 0,2 V a 200 mA. Vale para as versões v1.0 (exceção declarada à regra "a v1.0 é a mais barata que funciona", D138). **Sem o fusível no suporte, a placa fica sem 5 V**: use um fusível de 500 mA (ou um pedaço de fio na falta) e confira o valor ao trocar.

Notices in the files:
tools/gen_pinmap.py:
SPDX-License-Identifier: GPL-3.0-or-later
